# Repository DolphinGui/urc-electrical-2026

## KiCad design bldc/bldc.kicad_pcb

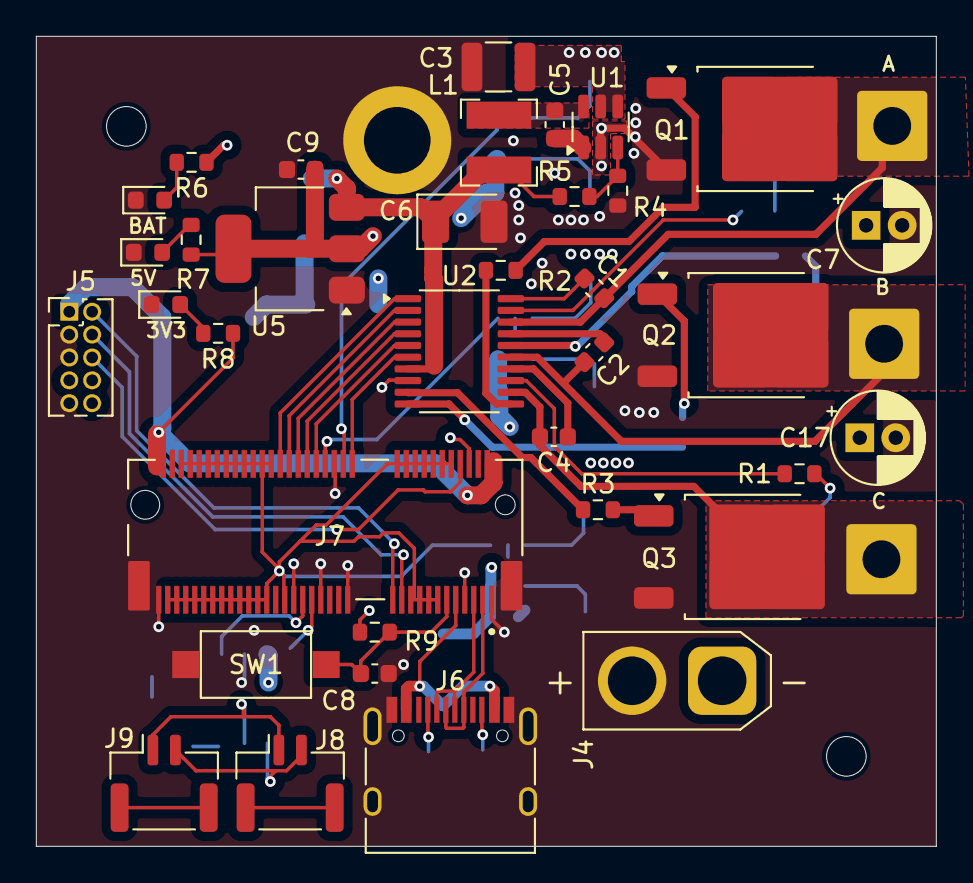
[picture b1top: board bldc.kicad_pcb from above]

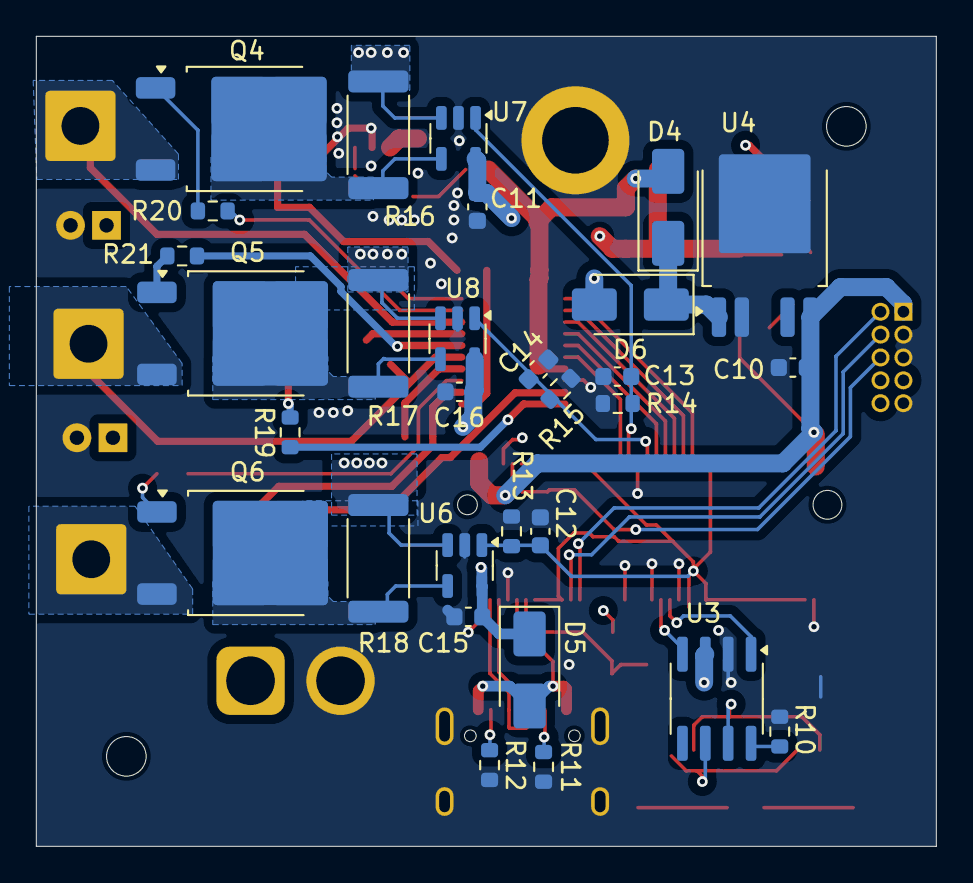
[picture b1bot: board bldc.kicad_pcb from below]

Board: 4 copper layers, 50.0 x 45.0 mm, 71 parts (30 on the bottom side), 57 nets.

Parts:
C1, C2, C4: 100nF; C_0603_1608Metric
C3: 4.7uF; C_1210_3225Metric
C5, C11, C15, C16: 0.1uF; C_0603_1608Metric
C6: 22uF; CP_EIA-3528-12_Kemet-T_Pad1.50x2.35mm_HandSolder
C7, C17: 22uF; CP_Radial_D5.0mm_P2.00mm
C8: C; C_0603_1608Metric
C9, C10: 2.2uF; C_0603_1608Metric
C12, C13, C14: TBD; C_0603_1608Metric
D1: BLUE; LED_0603_1608Metric
D2: GREEN; LED_0603_1608Metric
D3: RED; LED_0603_1608Metric
D4, D5, D6: D; D_SMA
H1, H2: MountingHole; MountingHole_2.2mm_M2
J1, J2, J3: MOTOR A; SolderWire-1.5sqmm_1x01_D1.7mm_OD3.9mm
J4: XT-30; AMASS_XT30U-M_1x02_P5.0mm_Vertical
J5: Conn_ARM_JTAG_SWD_10; PinHeader_2x05_P1.27mm_Vertical
J6: USB_C_Receptacle_USB2.0_16P; USB_C_Receptacle_HRO_TYPE-C-31-M-12
J7: MicroMod; micromod
J8, J9: CAN; JST_GH_SM02B-GHS-TB_1x02-1MP_P1.25mm_Horizontal
L1: 15uH; L_Bourns-SRN4018
Q1, Q2, Q3, Q4, Q5, Q6: Q_NMOS_GDS; TO-252-2
R1, R2, R3, R19, R20, R21: 10; R_0603_1608Metric
R4: 3.9k; R_0603_1608Metric
R5: 56k; R_0603_1608Metric
R6: 1.8k; R_0603_1608Metric
R7: 120; R_0603_1608Metric
R8: 68; R_0603_1608Metric
R9: 10k; R_0603_1608Metric
R10: 100; R_0603_1608Metric
R11, R12: 5.1k; R_0603_1608Metric
R13, R14, R15: 82k; R_0603_1608Metric
R16, R17, R18: 10m; R_2512_6332Metric
SW1: SW_Push; SW_SPST_CK_RS282G05A3
U1: LMR51610YDBVR; SOT-23-6
U2: DRV8300DPW; TSSOP-20_4.4x6.5mm_P0.65mm
U3: SN65HVD230; SOIC-8_3.9x4.9mm_P1.27mm
U4: LF33CPT-TR; TO-252AD
U5: AMS1117-5.0; SOT-223-3_TabPin2
U6, U7, U8: INA169; SOT-23-5

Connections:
+3V3: C10.1, J5.1 (VTref), J7.2 (VCC), J7.74 (VCC), R8.1, R9.2, U3.3 (VCC), U4.5 (VO)
+5V: C9.1, C11.1, C15.1, C16.1, D5.1 (K), D6.2 (A), R7.1, U5.2 (VO), U6.5 (V+), U7.5 (V+), U8.5 (V+)
+12V: C6.1, D4.2 (A), L1.2, R5.2, U2.7 (GVDD), U5.3 (VI)
+BATT: C3.2, C7.1, C17.1, J4.1, R6.1, R16.2, R17.2, R18.2, U1.4 (EN), U1.5 (VIN), U6.3 (+), U7.3 (+), U8.3 (+)
/Logic/A.BOOTSTRAP: C1.1, U2.20 (BSTA)
/Logic/A.GATEH: R20.1, U2.19 (GHA)
/Logic/A.GATEL: R2.1, U2.11 (GLA)
/Logic/A.SOURCE: C1.2, J1.1, Q1.2 (D), Q4.3 (S), U2.18 (SHA)
/Logic/B.BOOTSTRAP: C2.1, U2.17 (BSTB)
/Logic/B.GATEH: R21.1, U2.16 (GHB)
/Logic/B.GATEL: R19.1, U2.10 (GLB)
/Logic/B.SOURCE: C2.2, J2.1, Q2.2 (D), Q5.3 (S), U2.15 (SHB)
/Logic/C.BOOTSTRAP: C4.1, U2.14 (BSTC)
/Logic/C.GATEH: R1.1, U2.13 (GHC)
/Logic/C.GATEL: R3.1, U2.9 (GLC)
/Logic/C.SOURCE: C4.2, J3.1, Q3.2 (D), Q6.3 (S), U2.12 (SHC)
/Logic/CAN_RX: J7.41 (CAN_RX), U3.4 (R)
/Logic/CAN_TX: J7.43 (CAN_TX), U3.1 (D)
/Logic/CURRENT_A: C13.1, J7.34 (A0), R14.2, U7.1
/Logic/CURRENT_B: C14.1, J7.38 (A1), R15.2, U8.1
/Logic/CURRENT_C: C12.1, J7.10 (D0), J7.12 (I2C_SDA), J7.13 (UART_RTS), J7.14 (I2C_SCL), J7.15 (UART_CTS), J7.16 (I2C_INT), J7.17 (UART_TX), J7.18 (D1/CAM_TRIG), J7.19 (UART_RX), J7.20 (UART1_RX), J7.22 (UART1_TX), J7.47 (PWM1), J7.50 (AUD_BCLK/PCM_CLK/I2S_SCK/PDM_CLK), J7.51 (I2C1_SDA), J7.52 (AUD_LRCLK/PCM_SYNC/I2S_WS/PDM_DATA), J7.53 (I2C1_SCL), J7.54 (AUD_IN/PCM_IN/I2S_IN/CAM_PCLK), J7.55 (~SPI_CS), J7.56 (AUD_OUT/PCM_OUT/I2S_OUT/CAM_MCLK), J7.57 (SPI_SCK), J7.58 (AUD_MCLK), J7.59 (SPI_COPI), J7.60 (SPI1_SCK), J7.61 (SPI_CIPO), J7.62 (SPI1_COPI), J7.63 (G10/ADC_D+/CAM_VSYNC), J7.64 (SPI1_CIPO), J7.65 (G9/ADC_D-/CAM_HSYNC), J7.66 (SPI1_DATA1), J7.67 (G8), J7.68 (SPI1_DATA2), J7.69 (G7/BUS7), J7.70 (~SPI1_CS/SPI_DATA3), J7.71 (G6/BUS6), J7.73 (G5/BUS5), R13.2, U6.1
/Logic/INHA: J7.48 (G4/BUS4), U2.1 (INHA)
/Logic/INHB: J7.46 (G3/BUS3), U2.2 (INHB)
/Logic/INHC: J7.44 (G2/BUS2), U2.3 (INHC)
/Logic/INLA: J7.42 (G1/BUS1), U2.4 (INLA)
/Logic/INLB: J7.40 (G0/BUS0), U2.5 (INLB)
/Logic/INLC: J7.32 (PWM0), U2.6 (INLC)
/Logic/SWDCK: J5.4 (SWCLK/TCK), J7.21 (SWDCK)
/Logic/SWDIO: J5.2 (SWDIO/TMS), J7.23 (SWDIO)
/Logic/SWO: J5.6 (SWO/TDO), J7.8 (G11/SWO)
/Logic/USB.D+: J6.A6 (D+), J6.B6 (D+), J7.3 (USB_D+)
/Logic/USB.D-: J6.A7 (D-), J6.B7 (D-), J7.5 (USB_D-)
/Logic/USB.VUSB: D5.2 (A), J6.A4 (VBUS), J6.A9 (VBUS), J6.B4 (VBUS), J6.B9 (VBUS), J7.9 (USB_VIN)
/Logic/~BOOT: C8.1, J7.11 (~BOOT), R9.1, SW1.2
GND: C3.1, C6.2, C7.2, C8.2, C9.2, C10.2, C11.2, C12.2, C13.2, C14.2, C15.2, C16.2, C17.2, D1.1 (K), D2.1 (K), D3.1 (K), J4.2, J5.3 (GND), J5.5 (GND), J5.9 (GNDDetect), J6.A1 (GND), J6.A12 (GND), J6.B1 (GND), J6.B12 (GND), J6.S1 (SHIELD), J7.1 (GND), J7.7 (GND), J7.33 (GND), J7.36 (GND), J7.39 (GND), J7.45 (GND), J7.75 (GND), J7.S1 (GND), J7.S2 (GND), J7.S3 (GND), Q1.3 (S), Q2.3 (S), Q3.3 (S), R4.1, R10.1, R11.2, R12.2, R13.1, R14.1, R15.1, SW1.1, U1.2 (GND), U2.8 (GND), U3.2 (GND), U4.2 (EN), U4.3 (GND), U5.1 (GND), U6.2 (GND), U7.2 (GND), U8.2 (GND)
unnamed: D1.2 (A), R6.2
unnamed: D2.2 (A), R7.2
unnamed: D3.2 (A), R8.2
unnamed: D4.1 (K), D6.1 (K), U4.1 (VI)
unnamed: J5.10 (~RESET), J7.6 (~RESET)
unnamed: J6.A5 (CC1), R11.1
unnamed: J6.B5 (CC2), R12.1
unnamed: J8.1, J9.1, U3.7 (CANH)
unnamed: J8.2, J9.2, U3.6 (CANL)
unnamed: Q1.1 (G), R2.2
unnamed: Q2.1 (G), R19.2
unnamed: Q3.1 (G), R3.2
unnamed: Q4.2 (D), R16.1, U7.4 (-)
unnamed: Q4.1 (G), R20.2
unnamed: Q5.2 (D), R17.1, U8.4 (-)
unnamed: Q5.1 (G), R21.2
unnamed: Q6.2 (D), R18.1, U6.4 (-)
unnamed: Q6.1 (G), R1.2
unnamed: C5.1, U1.1 (CB)
unnamed: R4.2, R5.1, U1.3 (FB)
unnamed: C5.2, L1.1, U1.6 (SW)
unnamed: R10.2, U3.8 (Rs)

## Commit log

2024-12-11 a third adc pin is not guarenteed, fix by adding to all pins
